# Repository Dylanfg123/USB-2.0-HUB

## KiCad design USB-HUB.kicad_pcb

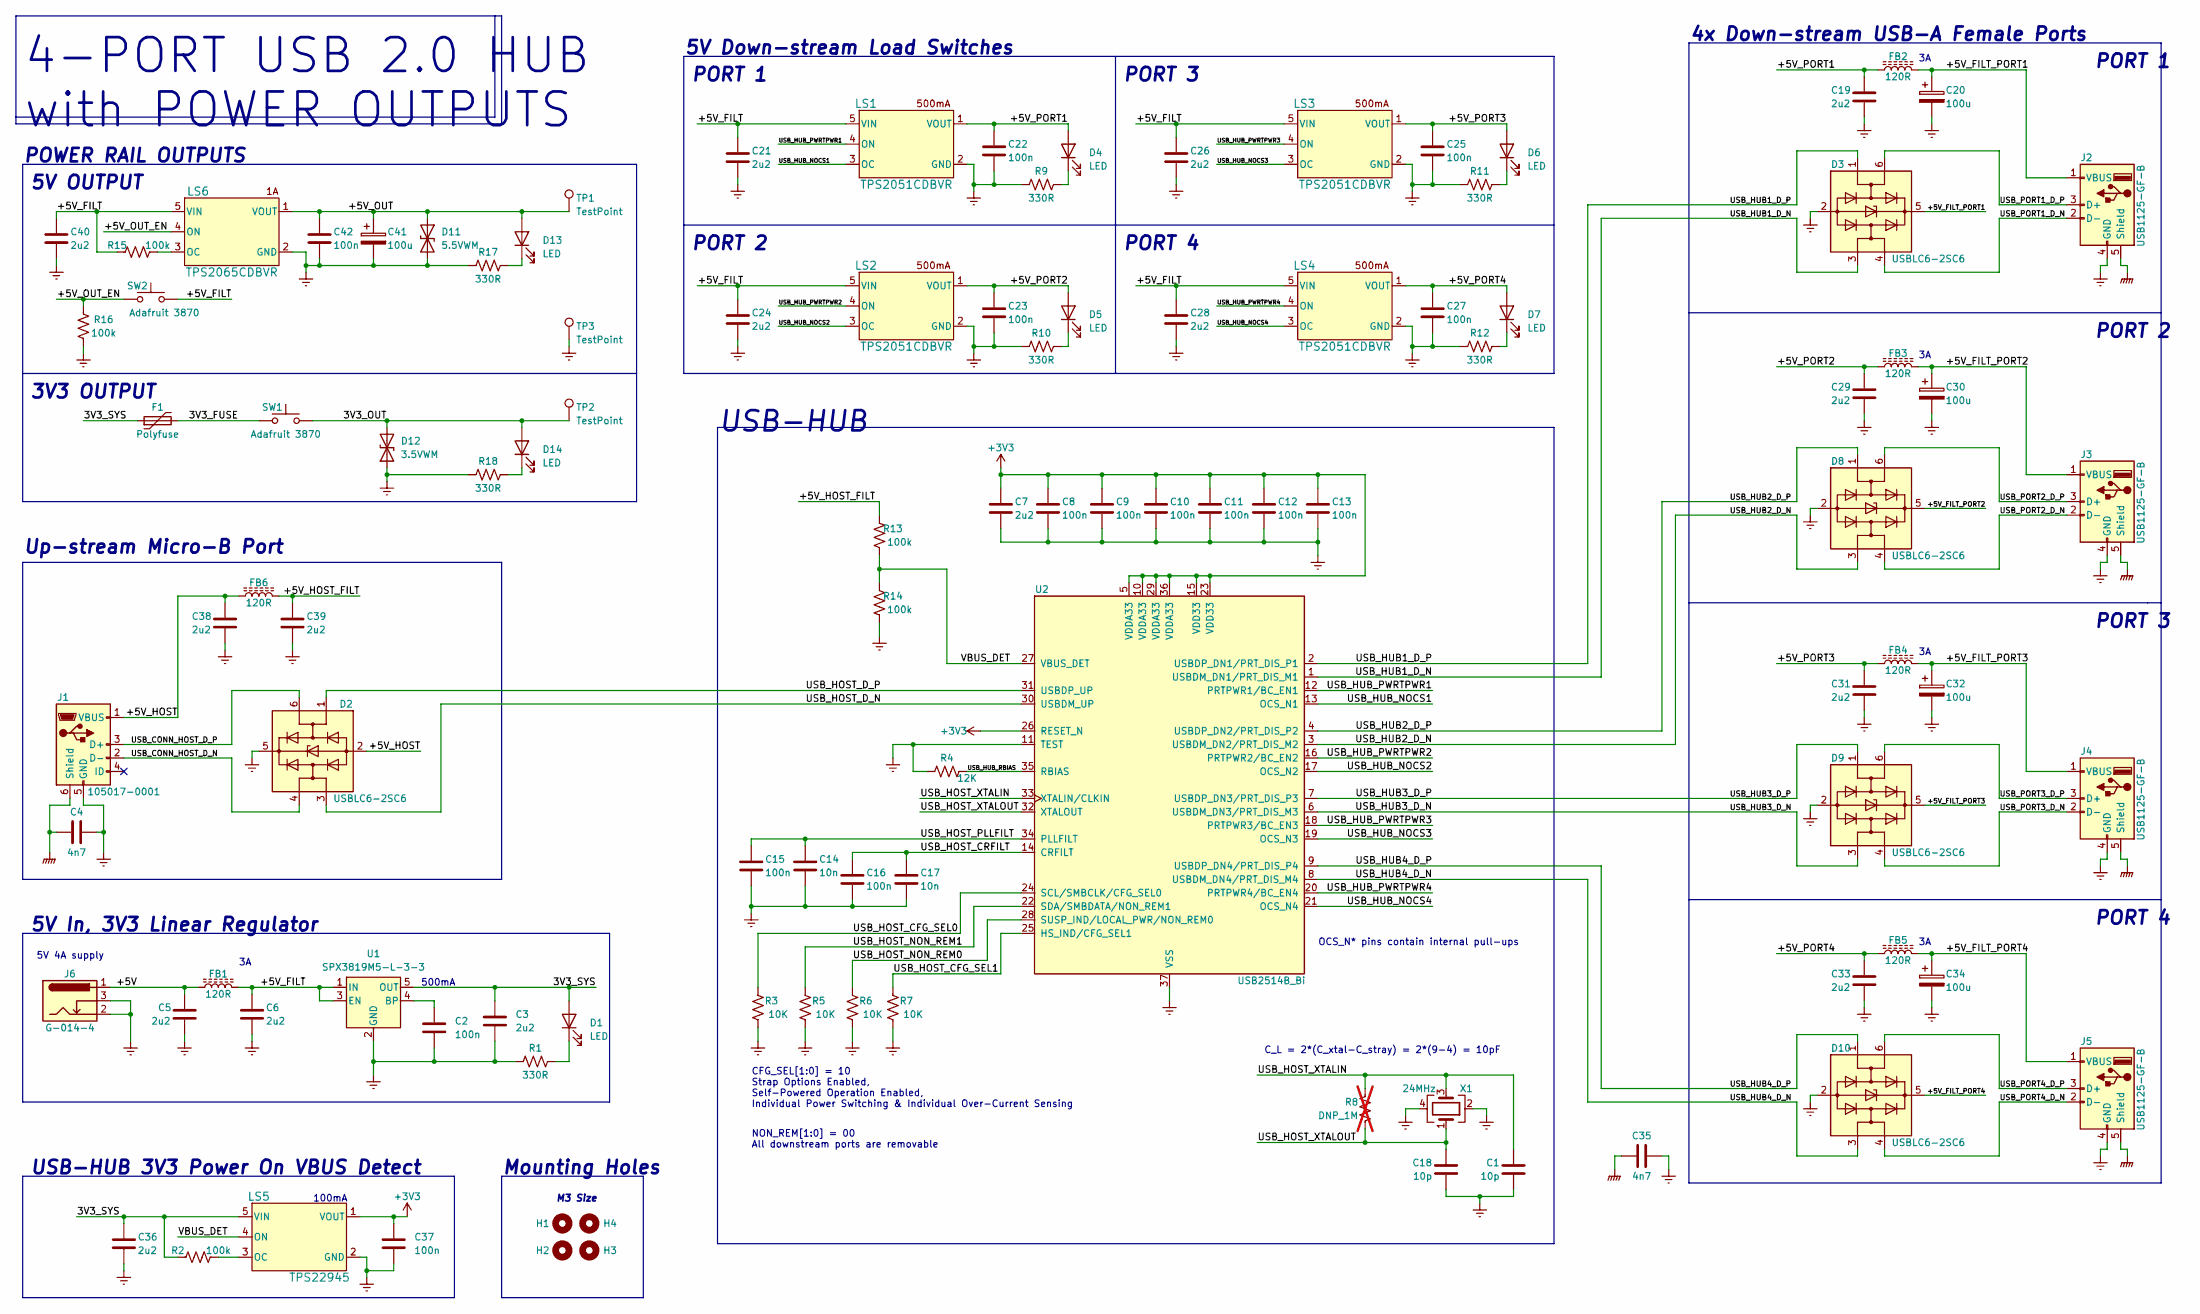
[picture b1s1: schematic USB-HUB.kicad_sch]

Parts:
C1, C18: 10p; C_0603_1608Metric; Manufacturer PN C0603C100K3GAC7867
C2, C8, C9, C10, C11, C12, C13, C15, C16, C22, C23, C25, C27, C37, C42: 100n; C_0603_1608Metric; Manufacturer PN CL10B104KA8NNNC
C3, C5, C6, C7, C19, C21, C24, C26, C28, C29, C31, C33, C36, C38, C39, C40: 2u2; C_0603_1608Metric; Manufacturer PN GRM188R61E225KA12D
C4, C35: 4n7; C_0603_1608Metric; Manufacturer PN 0603B472K250CT
C14, C17: 10n; C_0603_1608Metric; Manufacturer PN C0603C103J3GAC7867
C20, C30, C32, C34, C41: 100u; CP_Elec_6.3x7.7; Manufacturer PN UWT1E101MCL1GS
D1, D4, D5, D6, D7, D13, D14: LED; LED_0603_1608Metric; Manufacturer PN LTST-C190GKT
D2, D3, D8, D9, D10: USBLC6-2SC6; SOT-23-6; Manufacturer PN USBLC6-2SC6
D11: 5.5VWM; D_SOD-323_HandSoldering; Manufacturer PN SD05C-7
D12: 3.5VWM; D_SOD-923; Manufacturer PN DF2S5.6FS,L3M
F1: Polyfuse; Fuse_2920_7451Metric; Manufacturer PN 2920L030DR
FB1, FB2, FB3, FB4, FB5, FB6: 120R; L_0805_2012Metric; Manufacturer PN ILHB0805ER121V
H1, H2, H3, H4: MountingHole; MountingHole_3.2mm_M3
J1: 105017-0001; USB_Micro-B_Molex-105017-0001; Manufacturer PN 1050170001
J2, J3, J4, J5: USB1125-GF-B; USB_A_CONNFLY_DS1095-WNR0; Manufacturer PN USB1125-GF-B
J6: G-014-4; BarrelJack_Horizontal; Manufacturer PN G-014-4
LS1, LS2, LS3, LS4: TPS2051CDBVR; SOT-23-5; Manufacturer PN TPS2051CDBVR
LS5: TPS22945; SOT-353_SC-70-5; Manufacturer PN TPS22945DCKR
LS6: TPS2065CDBVR; SOT-23-5; Manufacturer PN TPS2065CDBVR
R1, R9, R10, R11, R12, R17, R18: 330R; R_0603_1608Metric; Manufacturer PN ESR03EZPJ331
R2, R13, R14, R15, R16: 100k; R_0603_1608Metric; Manufacturer PN ESR03EZPJ104
R3, R5, R6, R7: 10K; R_0603_1608Metric; Manufacturer PN ESR03EZPJ103
R4: 12K; R_0603_1608Metric; Manufacturer PN ESR03EZPJ123
R8: DNP_1M; R_0603_1608Metric; not fitted
SW1, SW2: Adafruit 3870; Adafruit_3870; Manufacturer PN 3870
TP1, TP2, TP3: TestPoint; TestPoint_Bridge_Pitch7.62mm_Drill1.3mm
U1: SPX3819M5-L-3-3; SOT-23-5; Manufacturer PN SPX3819M5-L-3-3/TR
U2: USB2514B_Bi; QFN-36-1EP_6x6mm_P0.5mm_EP3.7x3.7mm; Manufacturer PN USB2514B-AEZC-TR
X1: 24MHz; Crystal_SMD_3225-4Pin_3.2x2.5mm; Manufacturer PN TSX-3225 24.0000MF20G-AC0

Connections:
+3V3: C7.1, C8.1, C9.1, C10.1, C11.1, C12.1, C13.1, C37.1, LS5.1 (VOUT), U2.5 (VDDA33), U2.10 (VDDA33), U2.15 (VDD33), U2.23 (VDD33), U2.26 (RESET_N), U2.29 (VDDA33), U2.36 (VDDA33)
/3V3_FUSE: F1.2, SW1.1
/3V3_OUT: D12.2 (A2), D14.2 (A), SW1.2, TP2.1
/3V3_SYS: C3.1, C36.1, D1.2 (A), F1.1, LS5.5 (VIN), R2.2, U1.5 (OUT)
/+5V: C5.1, FB1.1, J6.1
/+5V_FILT: C6.1, C21.1, C24.1, C26.1, C28.1, C40.1, FB1.2, LS1.5 (VIN), LS2.5 (VIN), LS3.5 (VIN), LS4.5 (VIN), LS6.5 (VIN), R15.2, SW2.2, U1.1 (IN), U1.3 (EN)
/+5V_FILT_PORT1: C20.1, D3.5 (VBUS), FB2.2, J2.1 (VBUS)
/+5V_FILT_PORT2: C30.1, D8.5 (VBUS), FB3.2, J3.1 (VBUS)
/+5V_FILT_PORT3: C32.1, D9.5 (VBUS), FB4.2, J4.1 (VBUS)
/+5V_FILT_PORT4: C34.1, D10.5 (VBUS), FB5.2, J5.1 (VBUS)
/+5V_HOST: C38.1, D2.2 (GND), FB6.1, J1.1 (VBUS)
/+5V_HOST_FILT: C39.1, FB6.2, R13.2
/+5V_OUT: C41.1, C42.1, D11.1 (A1), D13.2 (A), LS6.1 (VOUT), TP1.1
/+5V_OUT_EN: LS6.4 (ON), R16.2, SW2.1
/+5V_PORT1: C19.1, C22.1, D4.2 (A), FB2.1, LS1.1 (VOUT)
/+5V_PORT2: C23.1, C29.1, D5.2 (A), FB3.1, LS2.1 (VOUT)
/+5V_PORT3: C25.1, C31.1, D6.2 (A), FB4.1, LS3.1 (VOUT)
/+5V_PORT4: C27.1, C33.1, D7.2 (A), FB5.1, LS4.1 (VOUT)
/USB_CONN_HOST_D_N: D2.4 (I/O2), J1.2 (D-)
/USB_CONN_HOST_D_P: D2.6 (I/O1), J1.3 (D+)
/USB_HOST_CFG_SEL0: R3.2, U2.24 (SCL/SMBCLK/CFG_SEL0)
/USB_HOST_CFG_SEL1: R7.2, U2.25 (HS_IND/CFG_SEL1)
/USB_HOST_CRFILT: C16.1, C17.1, U2.14 (CRFILT)
/USB_HOST_D_N: D2.3 (I/O2), U2.30 (USBDM_UP)
/USB_HOST_D_P: D2.1 (I/O1), U2.31 (USBDP_UP)
/USB_HOST_NON_REM0: R6.2, U2.28 (SUSP_IND/LOCAL_PWR/NON_REM0)
/USB_HOST_NON_REM1: R5.2, U2.22 (SDA/SMBDATA/NON_REM1)
/USB_HOST_PLLFILT: C14.1, C15.1, U2.34 (PLLFILT)
/USB_HOST_XTALIN: C1.1, R8.2, U2.33 (XTALIN/CLKIN), X1.3
/USB_HOST_XTALOUT: C18.1, R8.1, U2.32 (XTALOUT), X1.1
/USB_HUB1_D_N: D3.3 (I/O2), U2.1 (USBDM_DN1/PRT_DIS_M1)
/USB_HUB1_D_P: D3.1 (I/O1), U2.2 (USBDP_DN1/PRT_DIS_P1)
/USB_HUB2_D_N: D8.3 (I/O2), U2.3 (USBDM_DN2/PRT_DIS_M2)
/USB_HUB2_D_P: D8.1 (I/O1), U2.4 (USBDP_DN2/PRT_DIS_P2)
/USB_HUB3_D_N: D9.3 (I/O2), U2.6 (USBDM_DN3/PRT_DIS_M3)
/USB_HUB3_D_P: D9.1 (I/O1), U2.7 (USBDP_DN3/PRT_DIS_P3)
/USB_HUB4_D_N: D10.3 (I/O2), U2.8 (USBDM_DN4/PRT_DIS_M4)
/USB_HUB4_D_P: D10.1 (I/O1), U2.9 (USBDP_DN4/PRT_DIS_P4)
/USB_HUB_NOCS1: LS1.3 (OC), U2.13 (OCS_N1)
/USB_HUB_NOCS2: LS2.3 (OC), U2.17 (OCS_N2)
/USB_HUB_NOCS3: LS3.3 (OC), U2.19 (OCS_N3)
/USB_HUB_NOCS4: LS4.3 (OC), U2.21 (OCS_N4)
/USB_HUB_PWRTPWR1: LS1.4 (ON), U2.12 (PRTPWR1/BC_EN1)
/USB_HUB_PWRTPWR2: LS2.4 (ON), U2.16 (PRTPWR2/BC_EN2)
/USB_HUB_PWRTPWR3: LS3.4 (ON), U2.18 (PRTPWR3/BC_EN3)
/USB_HUB_PWRTPWR4: LS4.4 (ON), U2.20 (PRTPWR4/BC_EN4)
/USB_HUB_RBIAS: R4.1, U2.35 (RBIAS)
/USB_PORT1_D_N: D3.4 (I/O2), J2.2 (D-)
/USB_PORT1_D_P: D3.6 (I/O1), J2.3 (D+)
/USB_PORT2_D_N: D8.4 (I/O2), J3.2 (D-)
/USB_PORT2_D_P: D8.6 (I/O1), J3.3 (D+)
/USB_PORT3_D_N: D9.4 (I/O2), J4.2 (D-)
/USB_PORT3_D_P: D9.6 (I/O1), J4.3 (D+)
/USB_PORT4_D_N: D10.4 (I/O2), J5.2 (D-)
/USB_PORT4_D_P: D10.6 (I/O1), J5.3 (D+)
/VBUS_DET: LS5.4 (ON), R13.1, R14.2, U2.27 (VBUS_DET)
GNDPWR: C4.1, C35.1, J1.6 (Shield), J2.5 (Shield), J3.5 (Shield), J4.5 (Shield), J5.5 (Shield)
GNDREF: C1.2, C2.2, C3.2, C4.2, C5.2, C6.2, C7.2, C8.2, C9.2, C10.2, C11.2, C12.2, C13.2, C14.2, C15.2, C16.2, C17.2, C18.2, C19.2, C20.2, C21.2, C22.2, C23.2, C24.2, C25.2, C26.2, C27.2, C28.2, C29.2, C30.2, C31.2, C32.2, C33.2, C34.2, C35.2, C36.2, C37.2, C38.2, C39.2, C40.2, C41.2, C42.2, D2.5 (VBUS), D3.2 (GND), D8.2 (GND), D9.2 (GND), D10.2 (GND), D11.2 (A2), D12.1 (A1), J1.5 (GND), J2.4 (GND), J3.4 (GND), J4.4 (GND), J5.4 (GND), J6.2, J6.3, LS1.2 (GND), LS2.2 (GND), LS3.2 (GND), LS4.2 (GND), LS5.2 (GND), LS6.2 (GND), R1.1, R3.1, R4.2, R5.1, R6.1, R7.1, R9.1, R10.1, R11.1, R12.1, R14.1, R16.1, R17.1, R18.1, TP3.1, U1.2 (GND), U2.11 (TEST), U2.37 (VSS), X1.2, X1.4
unnamed: D1.1 (K), R1.2
unnamed: D4.1 (K), R9.2
unnamed: D5.1 (K), R10.2
unnamed: D6.1 (K), R11.2
unnamed: D7.1 (K), R12.2
unnamed: D13.1 (K), R17.2
unnamed: D14.1 (K), R18.2
unnamed: LS5.3 (OC), R2.1
unnamed: LS6.3 (OC), R15.1
unnamed: C2.1, U1.4 (BP)

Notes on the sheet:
5V OUTPUT
5V In, 3V3 Linear Regulator
NON_REM[1:0] = 00 All downstream ports are removable
POWER RAIL OUTPUTS
5V Down-stream Load Switches
PORT 2
OCS_N* pins contain internal pull-ups
M3 Size
C_L = 2*(C_xtal-C_stray) = 2*(9-4) = 10pF
5V 4A supply
PORT 4
PORT 1
PORT 3
100mA
3V3 OUTPUT
Mounting Holes
4-PORT USB 2.0 HUB with POWER OUTPUTS
USB-HUB
CFG_SEL[1:0] = 10 Strap Options Enabled, Self-Powered Operation Enabled, Individual Power Switching & Individual Over-Current Sensing
500mA
Up-stream Micro-B Port
USB-HUB 3V3 Power On VBUS Detect
4x Down-stream USB-A Female Ports

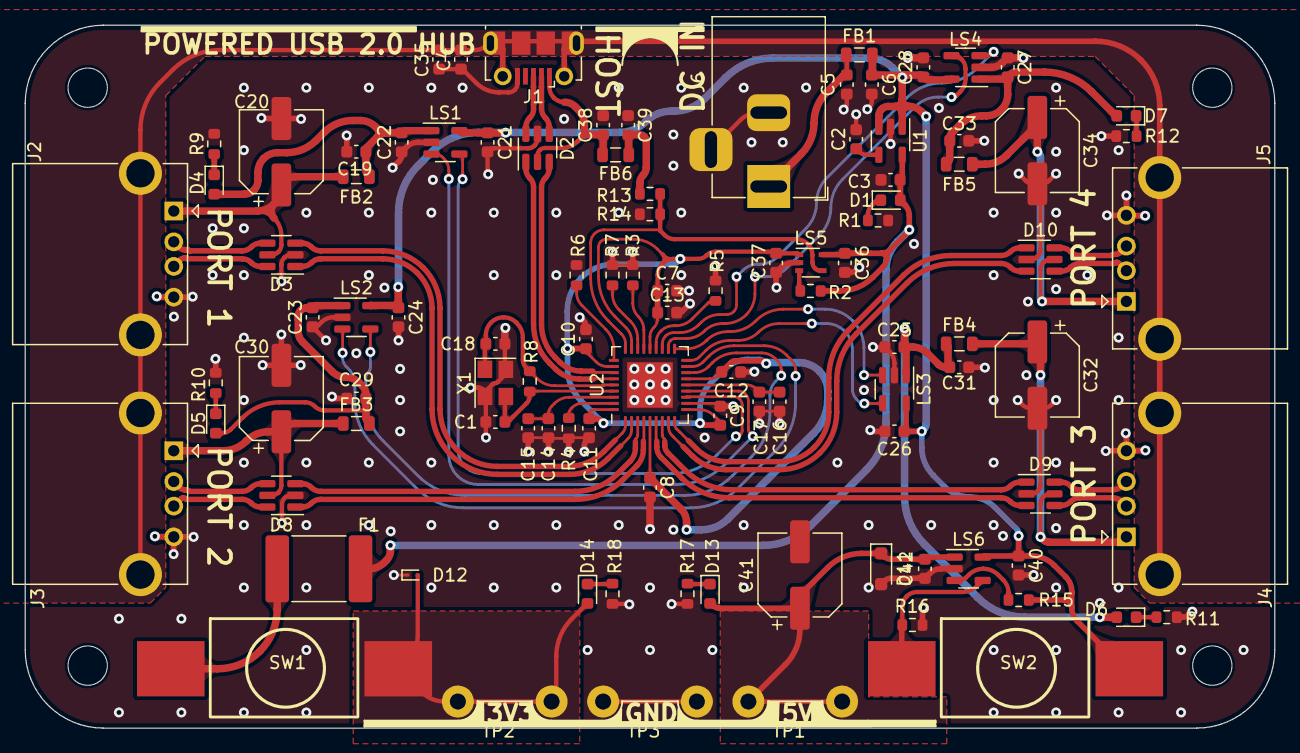
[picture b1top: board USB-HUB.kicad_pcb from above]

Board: 4 copper layers, 101.6 x 57.1 mm, 105 parts (0 on the bottom side), 68 nets.

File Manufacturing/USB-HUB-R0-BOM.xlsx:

USB-HUB-R0-BOM
null | References | Value | Manufacturer | Manufacturer PN | Distributor PN | Footprint | Quantity | kicad_dnp | Description
1 | C3, C5, C6, C7, C19, C21, C24, C26, C28, C29, C31, C33, C36, C38, C39, C40 | 2u2 | Murata Electronics | GRM188R61E225KA12D | 490-10731-1-ND | C_0603_1608Metric | 16 |  | CAP CER 2.2UF 25V X5R 0603
2 | C2, C8, C9, C10, C11, C12, C13, C15, C16, C22, C23, C25, C27, C37, C42 | 100n | Samsung Electro-Mechanics | CL10B104KA8NNNC | 1276-1006-1-ND | C_0603_1608Metric | 15 |  | CAP CER 0.1UF 25V X7R 0603
3 | C20, C30, C32, C34, C41 | 100u | Nichicon | UWT1E101MCL1GS | 493-2190-1-ND | CP_Elec_6.3x7.7 | 5 |  | CAP ALUM 100UF 20% 25V SMD
4 | C1, C18 | 10p | KEMET | C0603C100K3GAC7867 | 399-C0603C100K3GAC7867CT-ND | C_0603_1608Metric | 2 |  | 10 pF ±10% 25V Ceramic Capacitor C0G, NP0 0603 (1608 Metric)
5 | C4, C35 | 4n7 | Walsin Technology Corporation | 0603B472K250CT | 1292-1442-1-ND | C_0603_1608Metric | 2 |  | CAP CER 4700PF 25V X7R 0603
6 | C14, C17 | 10n | KEMET | C0603C103J3GAC7867 | 399-C0603C103J3GAC7867CT-ND | C_0603_1608Metric | 2 |  | CAP CER 10000PF 25V C0G/NP0 0603
7 | R1, R9, R10, R11, R12, R17, R18 | 330R | Rohm Semiconductor | ESR03EZPJ331 | RHM330DCT-ND | R_0603_1608Metric | 7 |  | RES 330 OHM 5% 1/4W 0603
8 | R2, R13, R14, R15, R16 | 100k | Rohm Semiconductor | ESR03EZPJ104 | RHM100KDCT-ND | R_0603_1608Metric | 5 |  | RES 100K OHM 5% 1/4W 0603
9 | R3, R5, R6, R7 | 10K | Rohm Semiconductor | ESR03EZPJ103 | RHM10KDCT-ND | R_0603_1608Metric | 4 |  | RES 10K OHM 5% 1/4W 0603
10 | R4 | 12K | Rohm Semiconductor | ESR03EZPJ123 | RHM12KDCT-ND | R_0603_1608Metric | 1 |  | RES 12K OHM 5% 1/4W 0603
11 | R8 | DNP_1M | - | - | - | R_0603_1608Metric | 1 | DNP | -
12 | D1, D4, D5, D6, D7, D13, D14 | LED | Lite-On Inc. | LTST-C190GKT | 160-1183-1-ND | LED_0603_1608Metric | 7 |  | Green 569nm LED Indication - Discrete 2.1V 0603 (1608 Metric)
13 | D2, D3, D8, D9, D10 | USBLC6-2SC6 | STMicroelectronics | USBLC6-2SC6 | 497-5235-1-ND | SOT-23-6 | 5 |  | TVS DIODE 5.25VWM 17VC SOT23-6
14 | D11 | 5.5VWM | Diodes Incorporated | SD05C-7 | 31-SD05C-7CT-ND | D_SOD-323_HandSoldering | 1 |  | TVS DIODE 5.5VWM 16VC SOD323
15 | D12 | 3.5VWM | Toshiba Semi | DF2S5.6FS,L3M | DF2S5.6FSL3MCT-ND | D_SOD-923 | 1 |  | TVS DIODE 3.5VWM SOD923
16 | U1 | SPX3819M5-L-3-3 | MaxLinear, Inc. | SPX3819M5-L-3-3/TR | 1016-1873-1-ND | SOT-23-5 | 1 |  | Linear Voltage Regulator IC Positive Fixed 1 Output 500mA SOT-23-5
17 | U2 | USB2514B_Bi | Microchip Technology | USB2514B-AEZC-TR | USB2514B-AEZC-CT-ND | QFN-36-1EP_6x6mm | 1 |  | USB Hub Controller USB Interface 36-QFN (6x6)
18 | X1 | 24MHz | EPSON | TSX-3225 24.0000MF20G-AC0 | SER4185CT-ND | Crystal_SMD_3225-4Pin_3.2x2.5mm | 1 |  | 24 MHz ±10ppm Crystal 9pF 40 Ohms 4-SMD, No Lead
19 | F1 | Polyfuse | Littelfuse Inc. | 2920L030DR | F2865CT-ND | Fuse_2920_7451Metric | 1 |  | Polymeric PTC Resettable Fuse 60V 300 mA Ih Surface Mount 2920 (7351 Metric), C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
20 | SW1, SW2 | Adafruit 3870 | Adafruit | 3870 | 3870 | Adafruit_3870 | 2 |  | Toggle On/Off switch, 12V 500mA max.
21 | FB1, FB2, FB3, FB4, FB5, FB6 | 120R | Vishay Dale | ILHB0805ER121V | 541-2299-1-ND | L_0805_2012Metric | 6 |  | 120 Ohms @ 100 MHz 1 Ferrite Bead 0805 (2012 Metric) 5A 20mOhm
22 | LS1, LS2, LS3, LS4 | TPS2051CDBVR | Texas Instruments | TPS2051CDBVR | 296-29537-1-ND | SOT-23-5 | 4 |  | IC PWR SWITCH N-CHAN 1:1 500mA SOT23-5
23 | TP1, TP2, TP3 | TestPoint |  |  |  | TestPoint_Bridge | 3
24 | LS5 | TPS22945 | Texas Instruments | TPS22945DCKR | 296-24475-1-ND | SOT-353_SC-70-5 | 1 |  | IC PWR SWITCH P-CHAN 1:1 100mA SC70-5
25 | LS6 | TPS2065CDBVR | Texas Instruments | TPS2065CDBVR | 296-39353-1-ND | SOT-23-5 | 1 |  | IC PWR SWITCH N-CHAN 1:1 1A SOT23-5
26 | J2, J3, J4, J5 | USB1125-GF-B | GCT | USB1125-GF-B | USB1125-GF-B | USB_A_CONNFLY_DS1095-WNR0 | 4 |  | USB-A (USB TYPE-A) USB 2.0 Receptacle Connector 4 Position Through Hole, Right 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
27 | J1 | 105017-0001 | Molex | 1050170001 | WM1399CT-ND | USB_Micro-B_Molex-105017-0001 | 1 |  | USB - micro B USB 2.0 Receptacle Connector 5 Position Surface Mount, Right Angl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
28 | J6 | G-014-4 | GlobTek, Inc. | G-014-4 | 1939-G-014-4-ND | BarrelJack_Horizontal | 1 |  | Power Barrel Connector Jack 2.10mm ID (0.083"), 5.50mm OD (0.217") Through Hole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

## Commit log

2024-04-26 REV 0: USB 2.0 Hub
